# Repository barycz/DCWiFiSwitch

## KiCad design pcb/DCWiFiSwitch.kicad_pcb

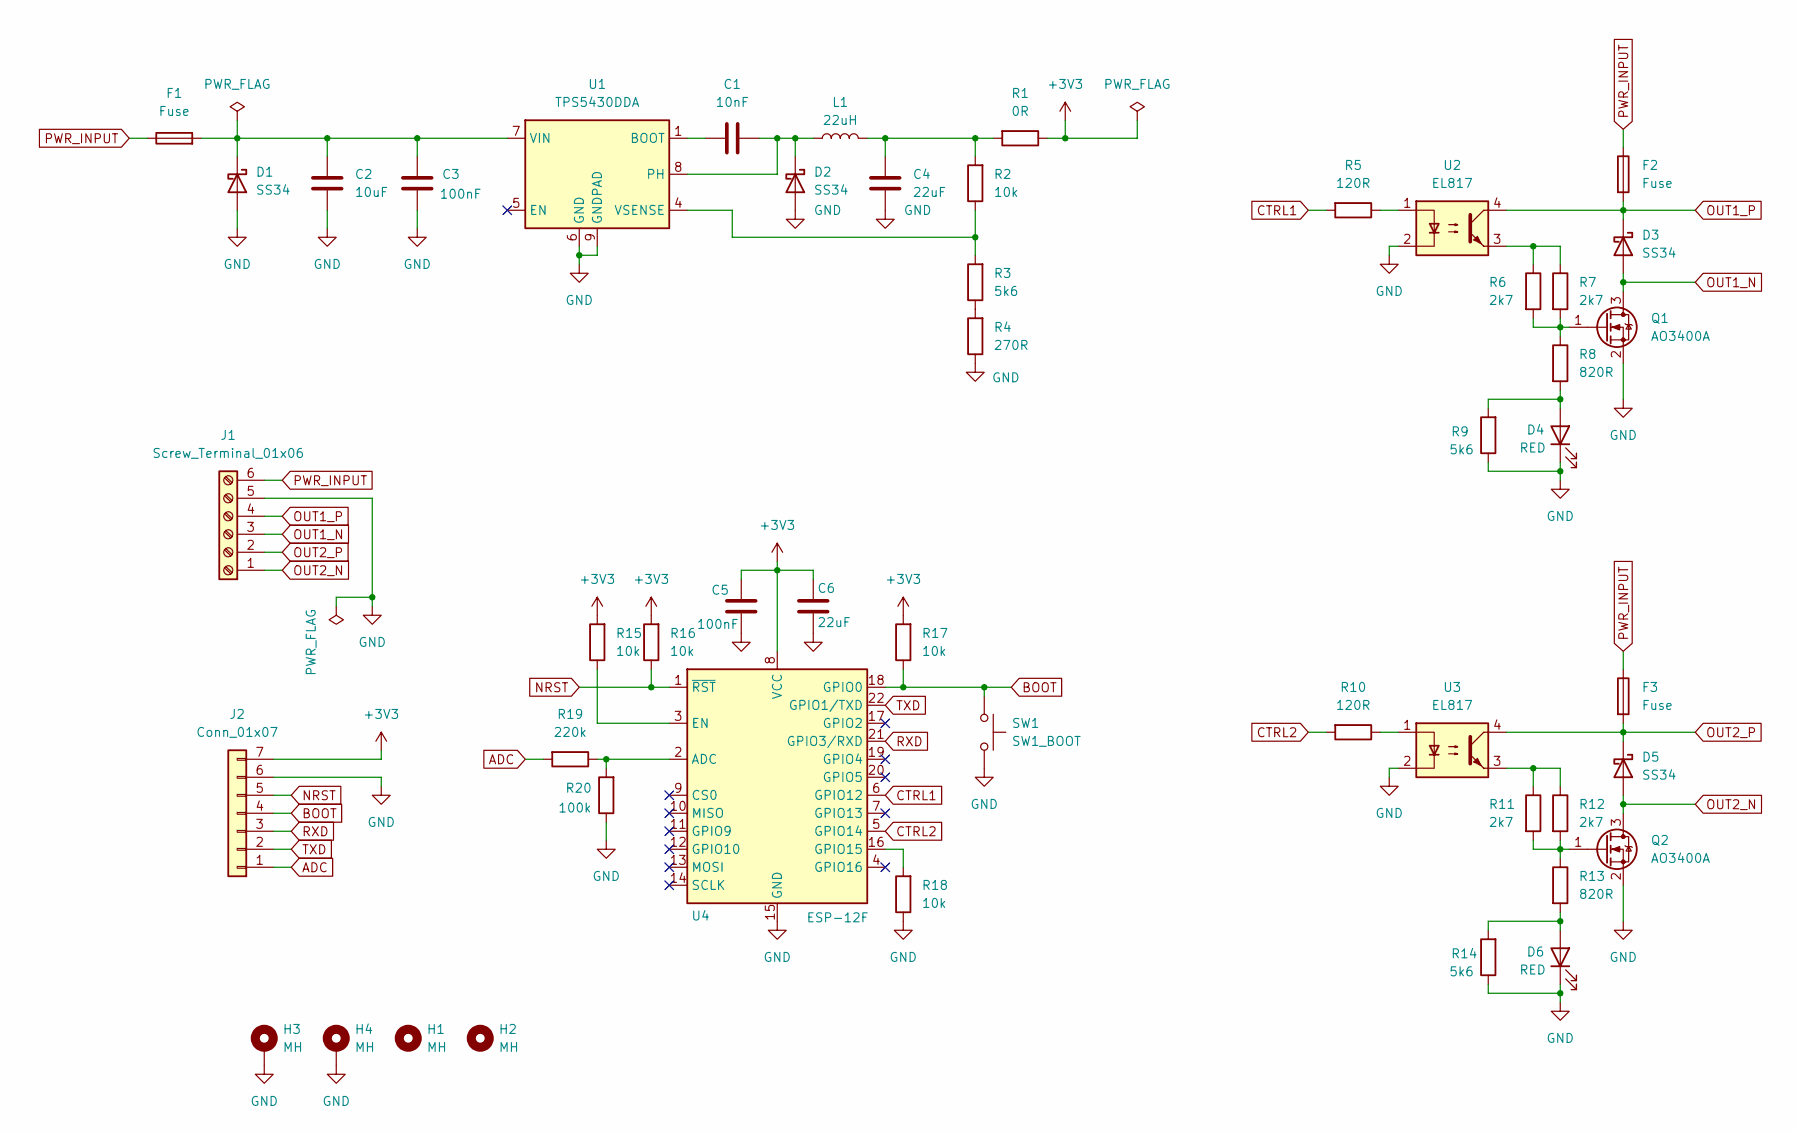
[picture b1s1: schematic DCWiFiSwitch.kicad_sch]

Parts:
C1: 10nF; C_0603_1608Metric; LCSC Part C57112
C2: 10uF; C_1206_3216Metric; LCSC Part C13585
C3, C5: 100nF; C_0603_1608Metric; LCSC Part C14663
C4, C6: 22uF; C_0603_1608Metric; LCSC Part C59461
D1, D2, D3, D5: SS34; D_SMA; LCSC Part C8678
D4, D6: RED; D_0603_1608Metric; LCSC Part C2286
F1, F2, F3: Fuse; Fuse_1206_3216Metric
H1, H2: MH; MountingHole_3.2mm_M3_ISO7380
H3, H4: MH; MountingHole_3.2mm_M3_ISO7380_Pad
J1: Screw_Terminal_01x06; TerminalBlock_Phoenix_MKDS-1,5-6-5.08_1x06_P5.08mm_Horizont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
J2: Conn_01x07; PinHeader_1x07_P2.54mm_Vertical
L1: 22uH; L_Sunlord_SWPA4030S; LCSC Part C83472
Q1, Q2: AO3400A; SOT-23; LCSC Part C20917
R1: 0R; R_0603_1608Metric; LCSC Part C21189
R2, R15, R16, R17, R18: 10k; R_0603_1608Metric; LCSC Part C25804
R3, R9, R14: 5k6; R_0603_1608Metric; LCSC Part C23189
R4: 270R; R_0603_1608Metric; LCSC Part C22966
R5, R10: 120R; R_0603_1608Metric; LCSC Part C22787
R6, R7, R11, R12: 2k7; R_0603_1608Metric; LCSC Part C13167
R8, R13: 820R; R_0603_1608Metric; LCSC Part C23253
R19: 220k; R_0603_1608Metric; LCSC Part C22961
R20: 100k; R_0603_1608Metric; LCSC Part C25803
SW1: SW1_BOOT; SW_Push_1P1T_XKB_TS-1187A; LCSC Part C318884
U1: TPS5430DDA; TI_SO-PowerPAD-8_ThermalVias; LCSC Part C9864
U2, U3: EL817; SMDIP-4_W9.53mm; LCSC Part C106900
U4: ESP-12F; ESP-12E

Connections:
+3V3: C5.2, C6.2, J2.7, R1.1, R15.2, R16.2, R17.2, U4.8 (VCC)
ADC: J2.1, R19.2
BOOT: J2.4, R17.1, SW1.1, U4.18 (GPIO0)
CTRL1: R5.2, U4.6 (GPIO12)
CTRL2: R10.2, U4.5 (GPIO14)
GND: C2.2, C3.2, C4.2, C5.1, C6.1, D1.2 (A), D2.2 (A), D4.1 (K), D6.1 (K), H3.1, H4.1, J1.5, J2.6, Q1.2 (S), Q2.2 (S), R4.1, R9.1, R14.1, R18.1, R20.1, SW1.2, U1.6 (GND), U1.9 (GNDPAD), U2.2, U3.2, U4.15 (GND)
NRST: J2.5, R16.1, U4.1 (~RST)
unnamed: C4.1, L1.2, R1.2, R2.2
unnamed: C2.1, C3.1, D1.1 (K), F1.2, U1.7 (VIN)
unnamed: C1.2, D2.1 (K), L1.1, U1.8 (PH)
unnamed: D4.2 (A), R8.2, R9.2
unnamed: D6.2 (A), R13.2, R14.2
unnamed: Q1.1 (G), R6.2, R7.2, R8.1
unnamed: Q2.1 (G), R11.2, R12.2, R13.1
unnamed: R3.1, R4.2
unnamed: R5.1, U2.1
unnamed: R6.1, R7.1, U2.3
unnamed: R10.1, U3.1
unnamed: R11.1, R12.1, U3.3
unnamed: C1.1, U1.1 (BOOT)
unnamed: R2.1, R3.2, U1.4 (VSENSE)
unnamed: R19.1, R20.2, U4.2 (ADC)
unnamed: R15.1, U4.3 (EN)
unnamed: R18.2, U4.16 (GPIO15)
OUT1_N: D3.2 (A), J1.3, Q1.3 (D)
OUT1_P: D3.1 (K), F2.2, J1.4, U2.4
OUT2_N: D5.2 (A), J1.1, Q2.3 (D)
OUT2_P: D5.1 (K), F3.2, J1.2, U3.4
PWR_INPUT: F1.1, F2.1, F3.1, J1.6
RXD: J2.3, U4.21 (GPIO3/RXD)
TXD: J2.2, U4.22 (GPIO1/TXD)

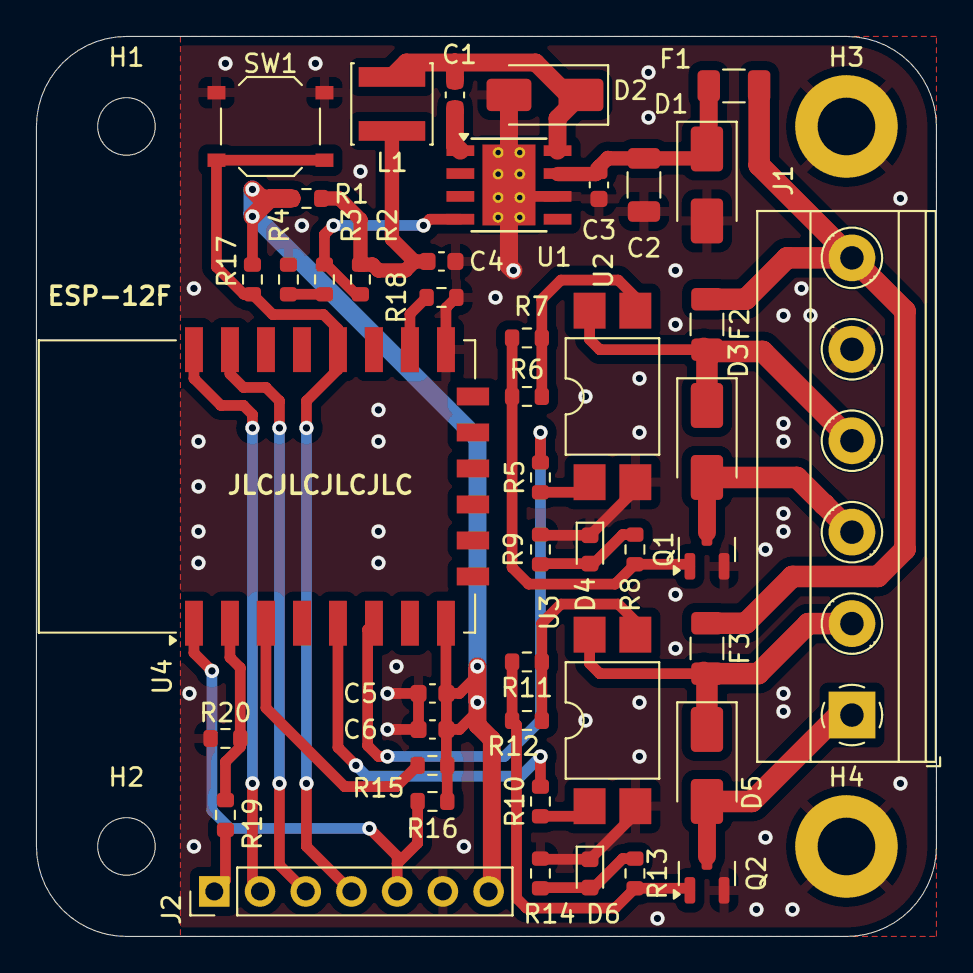
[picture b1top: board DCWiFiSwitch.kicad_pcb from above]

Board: 2 copper layers, 50.0 x 50.0 mm, 49 parts (0 on the bottom side), 31 nets.

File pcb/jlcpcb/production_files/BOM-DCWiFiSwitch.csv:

Comment,Designator,Footprint,LCSC
EL817,"U2,U3",SMDIP-4_W9.53mm,C106900
2k7,"R11,R12,R6,R7",R_0603_1608Metric,C13167
10uF,C2,C_1206_3216Metric,C13585
100nF,"C3,C5",C_0603_1608Metric,C14663
AO3400A,"Q1,Q2",SOT-23,C20917
0R,R1,R_0603_1608Metric,C21189
120R,"R10,R5",R_0603_1608Metric,C22787
RED,"D4,D6",D_0603_1608Metric,C2286
220k,R19,R_0603_1608Metric,C22961
270R,R4,R_0603_1608Metric,C22966
5k6,"R14,R3,R9",R_0603_1608Metric,C23189
820R,"R13,R8",R_0603_1608Metric,C23253
100k,R20,R_0603_1608Metric,C25803
10k,"R15,R16,R17,R18,R2",R_0603_1608Metric,C25804
SW1_BOOT,SW1,SW_Push_1P1T_XKB_TS-1187A,C318884
10nF,C1,C_0603_1608Metric,C57112
22uF,"C4,C6",C_0603_1608Metric,C59461
22uH,L1,L_Sunlord_SWPA4030S,C83472
SS34,"D1,D2,D3,D5",D_SMA,C8678
TPS5430DDA,U1,TI_SO-PowerPAD-8_ThermalVias,C9864

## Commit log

2024-07-22 Initial schematic, WIP
2024-07-23 ready for pcb
2024-07-23 board rc1
2024-07-24 board rc2
2024-07-24 board rc3
2024-07-25 fixed gpio programmer, board rc4
2024-07-25 added more silkscreen help and a push button, rc5
2024-07-26 exclude unwanted parts from bom and pos, board rc6
2024-07-26 add 3v3 to the pinheader, tweaked board
2024-07-28 add adc resistor divider
2024-07-28 add production files sent to the fab
2024-09-22 sample esphome configuration
